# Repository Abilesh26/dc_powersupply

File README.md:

# dc_powersupply
KiCAD for PCB layout of an AC to DC rectifier circuit

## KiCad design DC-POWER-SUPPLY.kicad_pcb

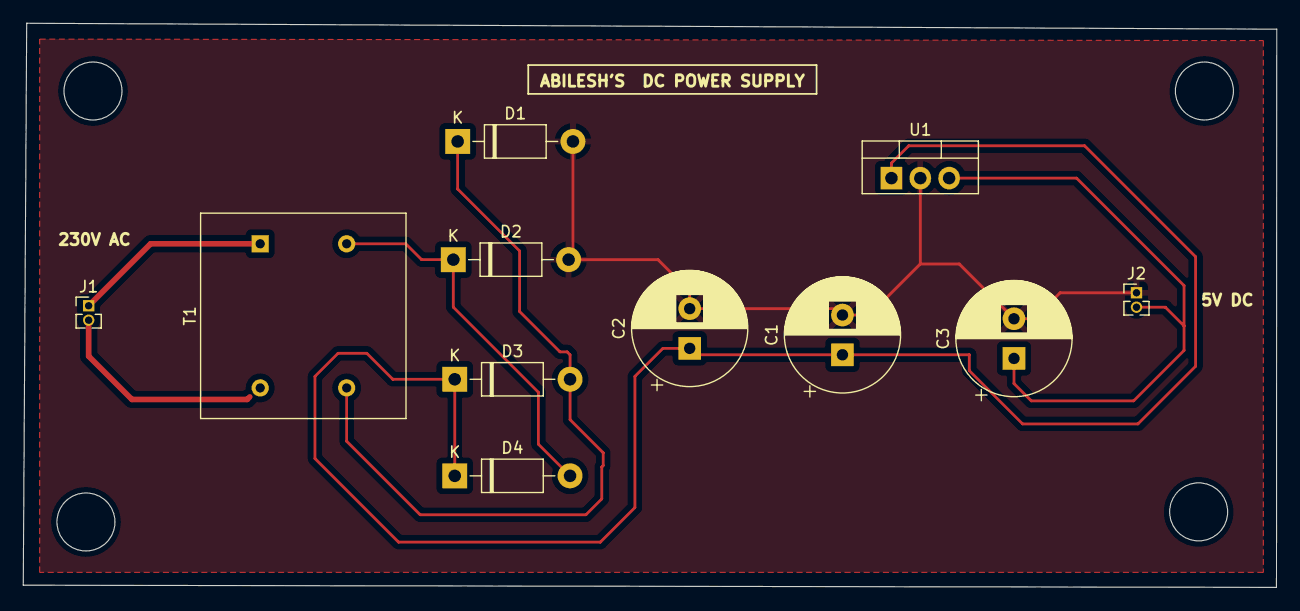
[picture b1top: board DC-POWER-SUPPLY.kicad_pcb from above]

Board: 2 copper layers, 110.4 x 49.7 mm, 11 parts (0 on the bottom side), 6 nets.

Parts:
C1: 470uF; CP_Radial_D10.0mm_P3.50mm
C2, C3: 0.01uF; CP_Radial_D10.0mm_P3.50mm
D1, D2, D3, D4: 1N4007; D_DO-41_SOD81_P10.16mm_Horizontal
J1, J2: Conn_01x02_Male; PinHeader_1x02_P1.27mm_Vertical
T1: Transformer_1P_1S; Transformer_NF_ETAL_1-1_P1200
U1: LM7805_TO220; TO-220-3_Vertical

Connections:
GND: C1.2, C2.2, C3.2, D1.2 (A), D2.2 (A), J2.1, U1.2 (GND)
unnamed: C1.1, C2.1, D3.1 (K), D4.1 (K), U1.1 (VI)
unnamed: C3.1, J2.2, U1.3 (VO)
unnamed: D1.1 (K), D3.2 (A), T1.4 (SB)
unnamed: D2.1 (K), D4.2 (A), T1.3 (SA)
unnamed: J1.1, T1.1 (AA)
